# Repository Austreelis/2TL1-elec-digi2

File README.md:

# Electronique Digitale II
*__Groupe 2TL1 - 4__*

## Setting up

### With Nix

> You will need to [install nix](nixos.org/download), which is safe to install
> alongside your usual package manager (if any).

The devshell provides a python 3.10 interpreter, the [black](TODO) code formatter,
the micropython implementation and its remote shell [rshell](https://github.com/dhylands/rshell/blob/master/README.rst);
and generally a suitable reproducible environment for hacking around.

To enter the devshell, run:

```
nix develop github:austreelis/2tl1-elec-digi2
```

## Useful links

[Raspberry Pi Pico Python SDK documentation](https://datasheets.raspberrypi.com/pico/raspberry-pi-pico-python-sdk.pdf)

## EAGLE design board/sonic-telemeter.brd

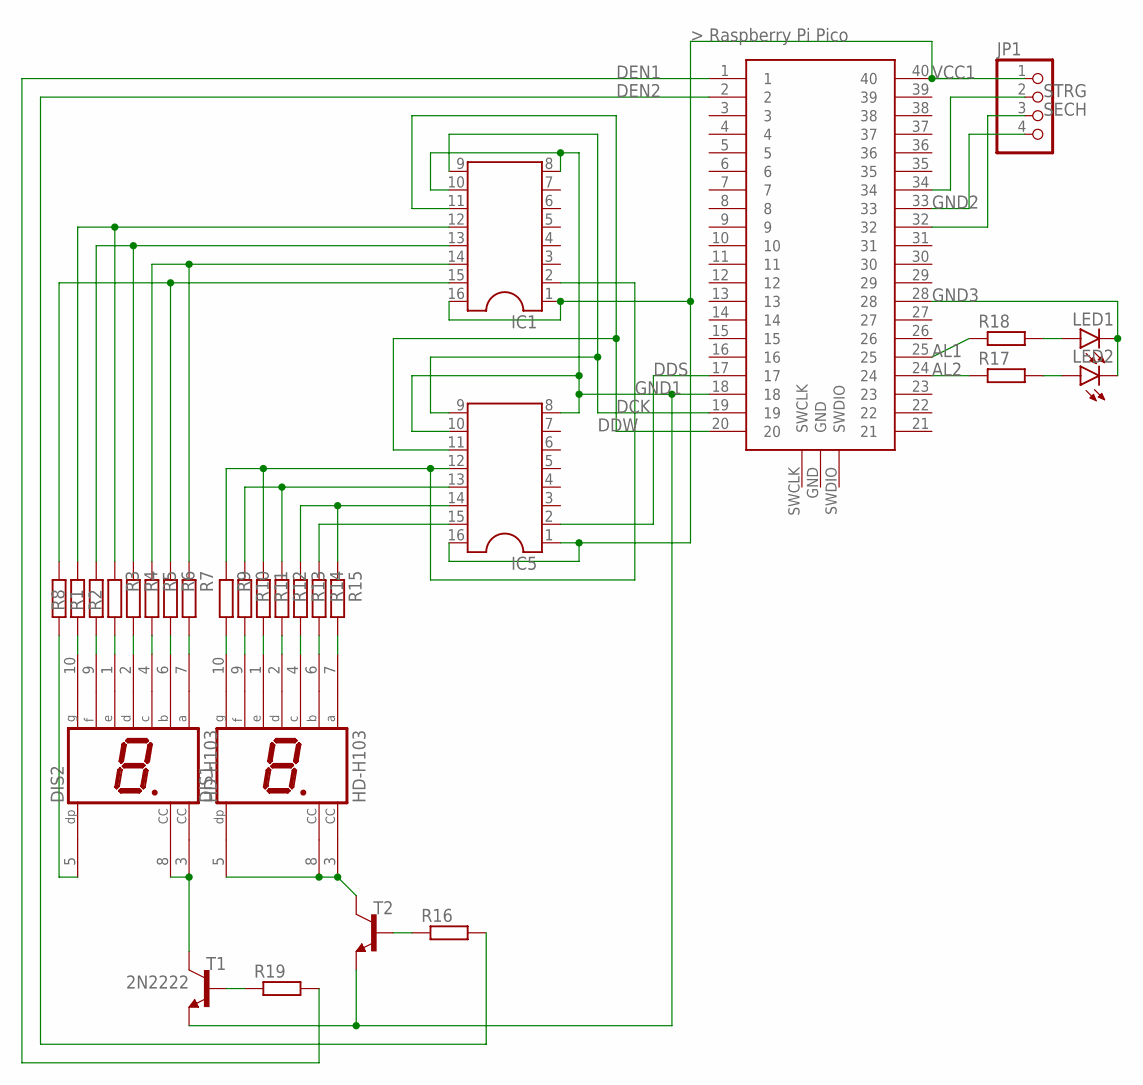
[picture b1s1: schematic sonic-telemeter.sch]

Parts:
DIS1, DIS2: HD-H103; HDSP-M
IC1, IC5: DIL16
JP1: PINHD-1X4; 1X04
LED1, LED2: LED5MM
R1, R2, R3, R4, R5, R6, R7, R8, R9, R10, R11, R12, R13, R14, R15, R16, R17, R18, R19: R-EU_0204/5; 0204/5
T1, T2: 2N2222; TO18
U$1: RASPBERRY-PI-PICO_TH; FT_RASPBERRY-PI-PICO_TH

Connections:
AL1: R18.1, U$1.25
AL2: R17.1, U$1.24
DCK: IC1.9, IC5.9, U$1.19
DDS: IC5.2, U$1.17
DDW: IC1.11, IC5.11, U$1.20
DEN1: R19.2, U$1.1
DEN2: R16.2, U$1.2
GND1: IC1.8, IC1.10, IC5.8, IC5.10, T1.1 (E), T2.1 (E), U$1.18
GND2: JP1.4, U$1.33
GND3: LED1.K (C), LED2.K (C), U$1.28
unnamed: IC1.15, R6.1, R8.1
unnamed: IC1.14, R5.1, R7.1
unnamed: IC1.13, R2.1, R4.1
unnamed: IC1.12, R1.1, R3.1
unnamed: IC5.13, R10.1, R12.1
unnamed: IC5.15, R14.1
unnamed: DIS2.3 (CC), DIS2.8 (CC), T1.3 (C)
unnamed: DIS1.3 (CC), DIS1.5 (DP), DIS1.8 (CC), T2.3 (C)
unnamed: DIS2.10 (G), R1.2
unnamed: DIS2.9 (F), R2.2
unnamed: DIS2.1 (E), R3.2
unnamed: DIS2.2 (D), R4.2
unnamed: DIS2.4 (C), R5.2
unnamed: DIS2.6 (B), R6.2
unnamed: DIS2.7 (A), R7.2
unnamed: R16.1, T2.2 (B)
unnamed: DIS2.5 (DP), R8.2
unnamed: R19.1, T1.2 (B)
unnamed: DIS1.10 (G), R9.2
unnamed: DIS1.9 (F), R10.2
unnamed: DIS1.1 (E), R11.2
unnamed: DIS1.2 (D), R12.2
unnamed: DIS1.4 (C), R13.2
unnamed: DIS1.6 (B), R14.2
unnamed: DIS1.7 (A), R15.2
unnamed: LED2.A, R17.2
unnamed: LED1.A, R18.2
unnamed: IC1.2, IC5.12, R9.1, R11.1
unnamed: IC5.14, R13.1, R15.1
SECH: JP1.3, U$1.32
STRG: JP1.2, U$1.34
VCC1: IC1.1, IC1.16, IC5.1, IC5.16, JP1.1, U$1.40

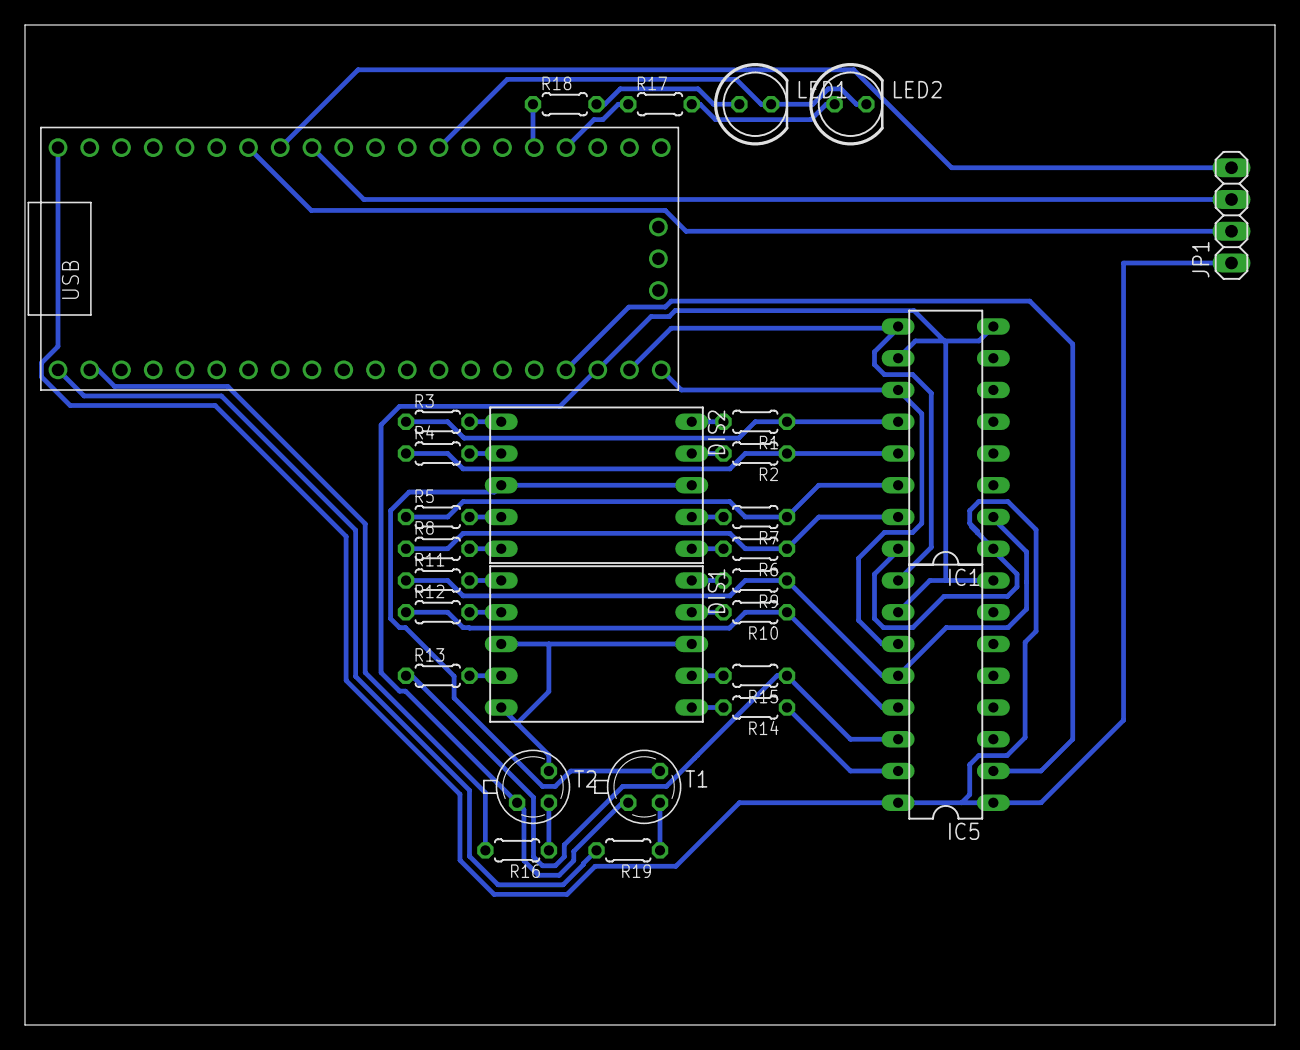
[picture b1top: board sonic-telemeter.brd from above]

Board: 2 copper layers, 100.0 x 80.0 mm, 29 parts (0 on the bottom side), 42 nets.

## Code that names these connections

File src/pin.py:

from micropython import const
from machine import Pin as _Pin

from log import debug

class Pin:
    PULL_DOWN = _Pin.PULL_DOWN
    PULL_UP = _Pin.PULL_UP
    
    IN = _Pin.IN
    OUT = _Pin.OUT
    
    def __init__(
        self,
        id: int,
        mode: int = _Pin.IN,
        pull: int | None = None,
        name: str | None = None,
    ):
        self.id = id
        self.pin = _Pin(id, mode, pull)
        self.name = name if name is not None else f"pin<{id}>"
        debug(f"Created pin {repr(self)}")

    def init(self, mode: int | None = None, pull: int | None = None):
        args = ()
        kwargs= {}
        if mode is not None:
            if pull is not None:
                args = (mode, pull)
            else:
                args = (mode,)
        elif pull is not None:
            kwargs["pull"] = pull
        self.pin.init(*args, **kwargs)

    def value(self, value: int = None):
        if value is None:
            return self.pin.value()
        return self.pin.value(*value)

    def toggle(self):
        self.pin.toggle()

    def low(self):
        self.pin.low()

    def high(self):
        self.pin.high()

    def __str__(self):
        return self.name

    def __repr__(self):
        return f"{self.name} {{ id: {self.id}, value: {self.value()} }}"

# Shift-registers control Pins
##Display data write
DDW = Pin(15, Pin.OUT, name="DDW")
##Display data clock
DCK = Pin(14, Pin.OUT, name="DCK") 
##Display data serial
DDS = Pin(13, Pin.OUT, name="DDS")

# 7-segment display control Pins
##Leftmost display enable
DEN0 = Pin(0, Pin.OUT, name="DEN0")
##Rightmost display enable
DEN1 = Pin(1, Pin.OUT, name="DEN1")

# LED Pins
##Green LED
LAL0 = Pin(19, Pin.OUT, name="LAL0")
##Red LED
LAL1 = Pin(18, Pin.OUT, name="LAL1")
##Green on-board LED
LSTA = Pin(25, Pin.OUT, name="LSTA")

# Ultrasonic distance probe Pins
##ECHO Pin
SECH = Pin(27, Pin.IN, name="SECH")
##TRIG Pin
STRG = Pin(28, Pin.OUT, name="STRG")

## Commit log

2023-02-08 init README
2023-02-08 init nix flake
2023-02-08 Add examples from course
2023-02-08 ignore nix devshell data dir
2023-02-13 [devshell] include the rp2040 emulator
2023-02-26 [sim] Init diagram.json
2023-03-12 First schématic
2023-03-12 Update board schematic
2023-03-13 Finalize board schematic for intermediary report
2023-03-13 Write up intermediary report
2023-03-13 rapport-intermediaire/main.tex: fix typo
2023-05-15 Fix board
2023-05-15 Telemeter micropython script
2023-05-15 Add flashing script
